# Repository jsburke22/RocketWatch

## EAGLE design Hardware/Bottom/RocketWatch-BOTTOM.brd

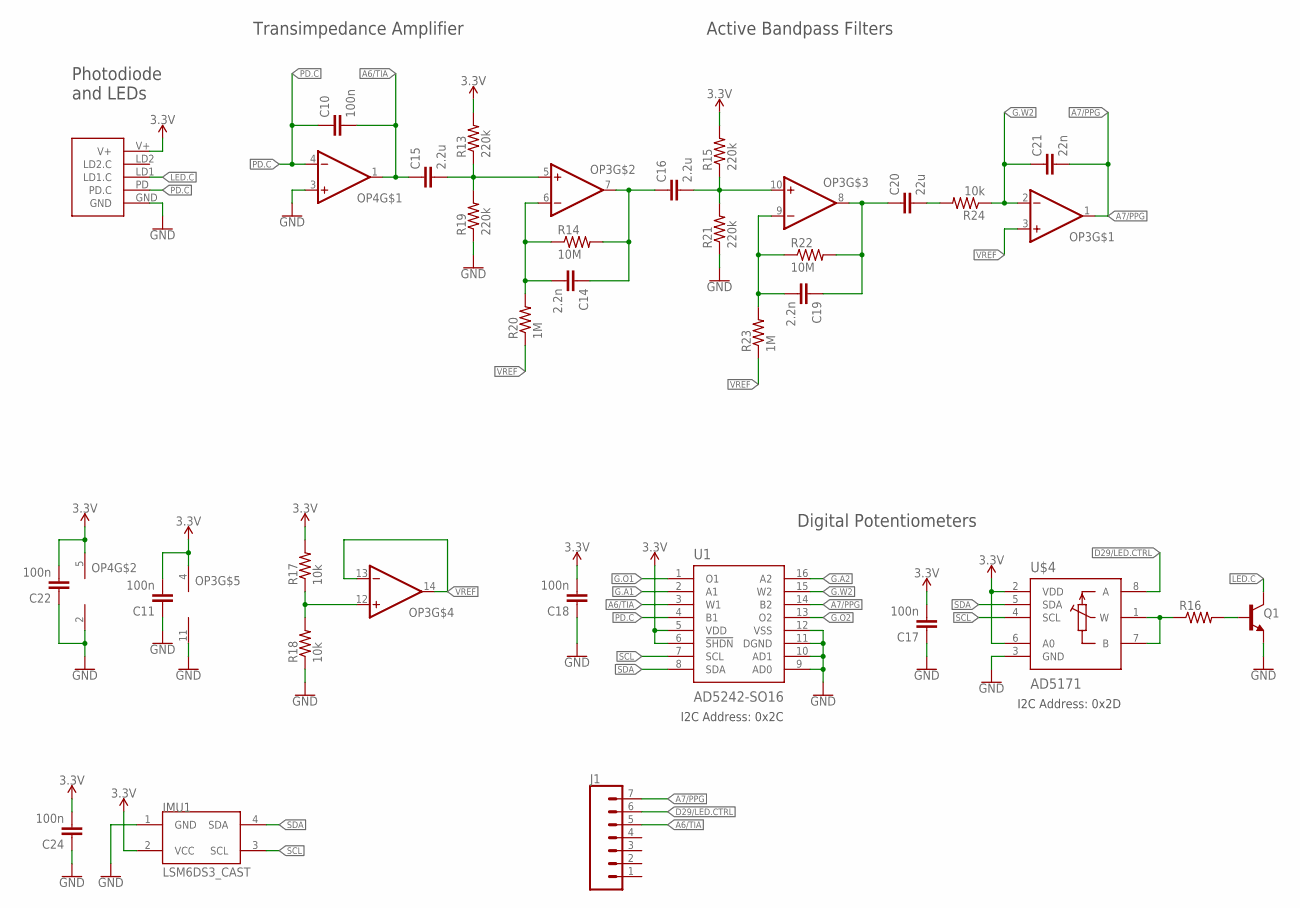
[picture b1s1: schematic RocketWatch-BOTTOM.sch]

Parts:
C10, C11, C17, C18, C22, C24: 100n; C0603
C14, C19: 2.2n; C0603
C15, C16: 2.2u; C0603
C20: 22u; C0603
C21: 22n; C0603
IMU1: LSM6DS3_CAST
J1: CONN_07; 1X07
OP3: OP-QUAD-SO14; SO14
OP4: OP-SINGLEOT; SOT23-5
Q1: NPN-GENERIC; SOT23-3
R13, R15, R19, R21: 220k; R0603
R14, R22: 10M; R0603
R16: RESISTOR0603; R0603
R17, R18: 10k; R0402
R20, R23: 1M; R0603
R24: 10k; R0603
U1: AD5242-SO16; SO16
U$3: PPG.MODULE.2
U$4: AD5171; SOT-23-8

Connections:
3.3V: C11.2, C17.2, C18.2, C22.2, C24.2, IMU1.2 (VCC), OP3.4 (V+), OP4.5 (V+), R13.2, R15.2, R17.2, U1.5 (VDD), U1.6 (!SHDN), U$3.V+, U$4.2 (VDD), U$4.6 (A0)
A6/TIA: C10.2, C15.1, J1.5, OP4.1 (OUT), U1.3 (W1)
A7/PPG: C21.2, J1.7, OP3.1 (OUT), U1.14 (B2)
D29/LED.CTRL: J1.6, U$4.8 (A)
G.A1: U1.2 (A1)
G.A2: U1.16 (A2)
G.O1: U1.1 (O1)
G.O2: U1.13 (O2)
G.W2: C21.1, OP3.2 (-IN), R24.1, U1.15 (W2)
GND: C11.1, C17.1, C18.1, C22.1, C24.1, IMU1.1 (GND), OP3.11 (V-), OP4.2 (V-), OP4.3 (+IN), Q1.2 (E), R18.1, R19.1, R21.1, U1.9 (AD0), U1.10 (AD1), U1.11 (DGND), U1.12 (VSS), U$3.GND, U$4.3 (GND)
LED.C: Q1.3 (C), U$3.LD1 (LD1.C)
unnamed: Q1.1 (B), R16.2
unnamed: R16.1, U$4.1 (W), U$4.7 (B)
unnamed: OP3.12 (+IN), R17.1, R18.2
unnamed: C15.2, OP3.5 (+IN), R13.1, R19.2
unnamed: C14.2, OP3.6 (-IN), R14.1, R20.2
unnamed: C14.1, C16.1, OP3.7 (OUT), R14.2
unnamed: C16.2, OP3.10 (+IN), R15.1, R21.2
unnamed: C19.2, OP3.9 (-IN), R22.1, R23.2
unnamed: C19.1, C20.1, OP3.8 (OUT), R22.2
unnamed: C20.2, R24.2
PD.C: C10.1, OP4.4 (-IN), U1.4 (B1), U$3.PD (PD.C)
SCL: IMU1.3 (SCL), U1.7 (SCL), U$4.4 (SCL)
SDA: IMU1.4 (SDA), U1.8 (SDA), U$4.5 (SDA)
VREF: OP3.3 (+IN), OP3.13 (-IN), OP3.14 (OUT), R20.1, R23.1

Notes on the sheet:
Photodiode and LEDs
Active Bandpass Filters
Digital Potentiometers
Transimpedance Amplifier
I2C Address: 0x2C
I2C Address: 0x2D

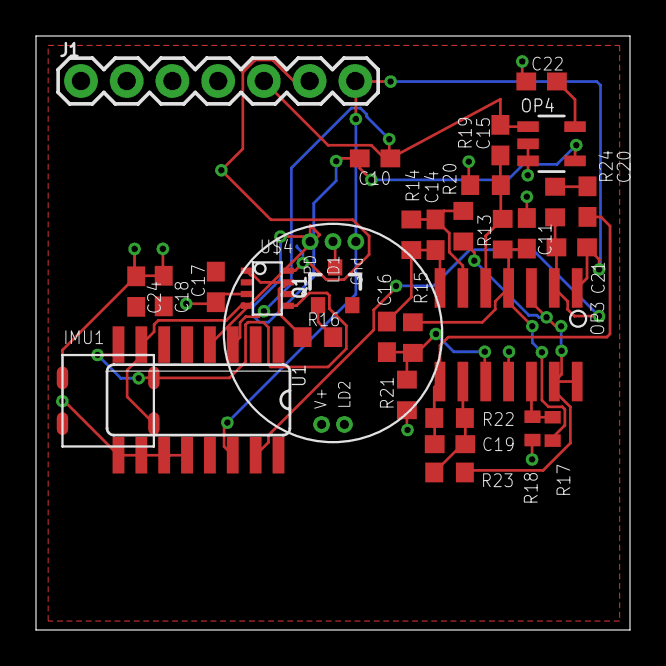
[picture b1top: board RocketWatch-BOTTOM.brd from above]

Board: 2 copper layers, 33.0 x 33.0 mm, 32 parts (0 on the bottom side), 21 nets.

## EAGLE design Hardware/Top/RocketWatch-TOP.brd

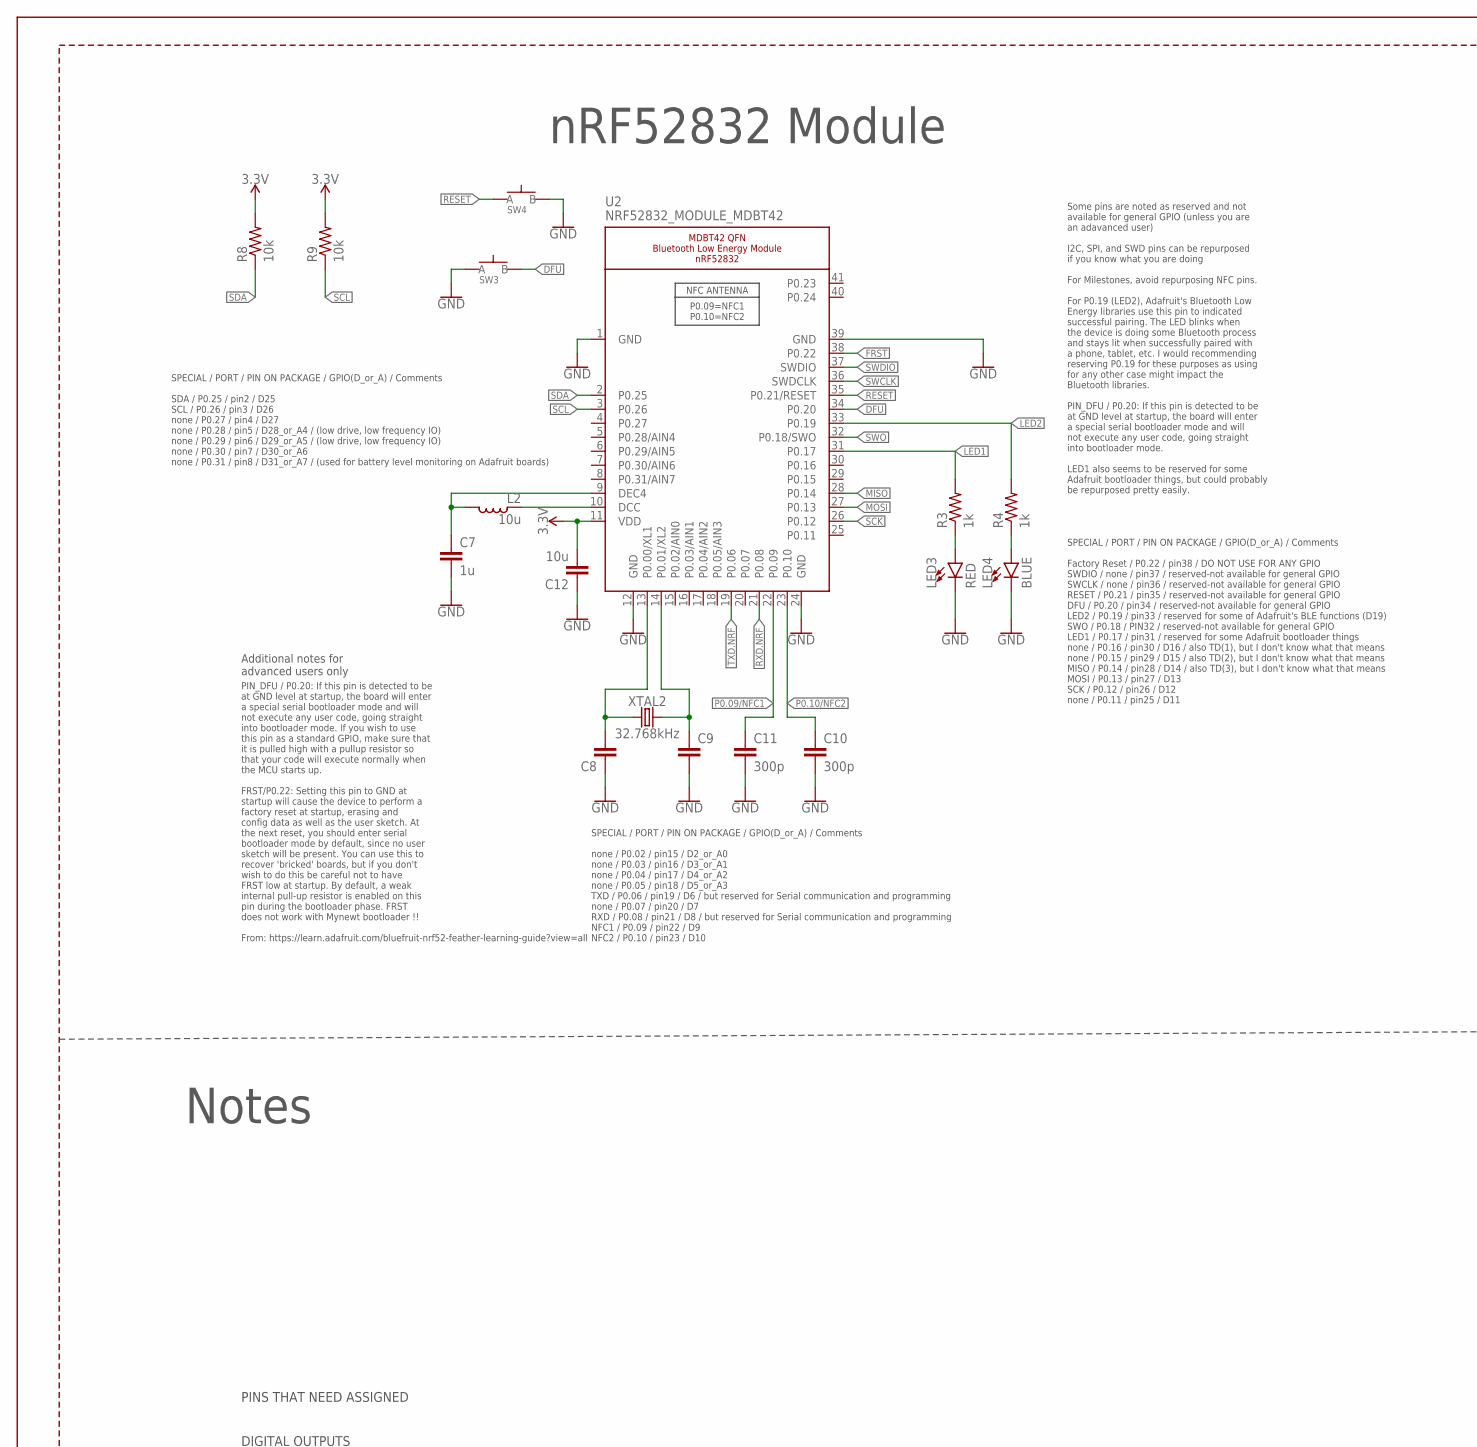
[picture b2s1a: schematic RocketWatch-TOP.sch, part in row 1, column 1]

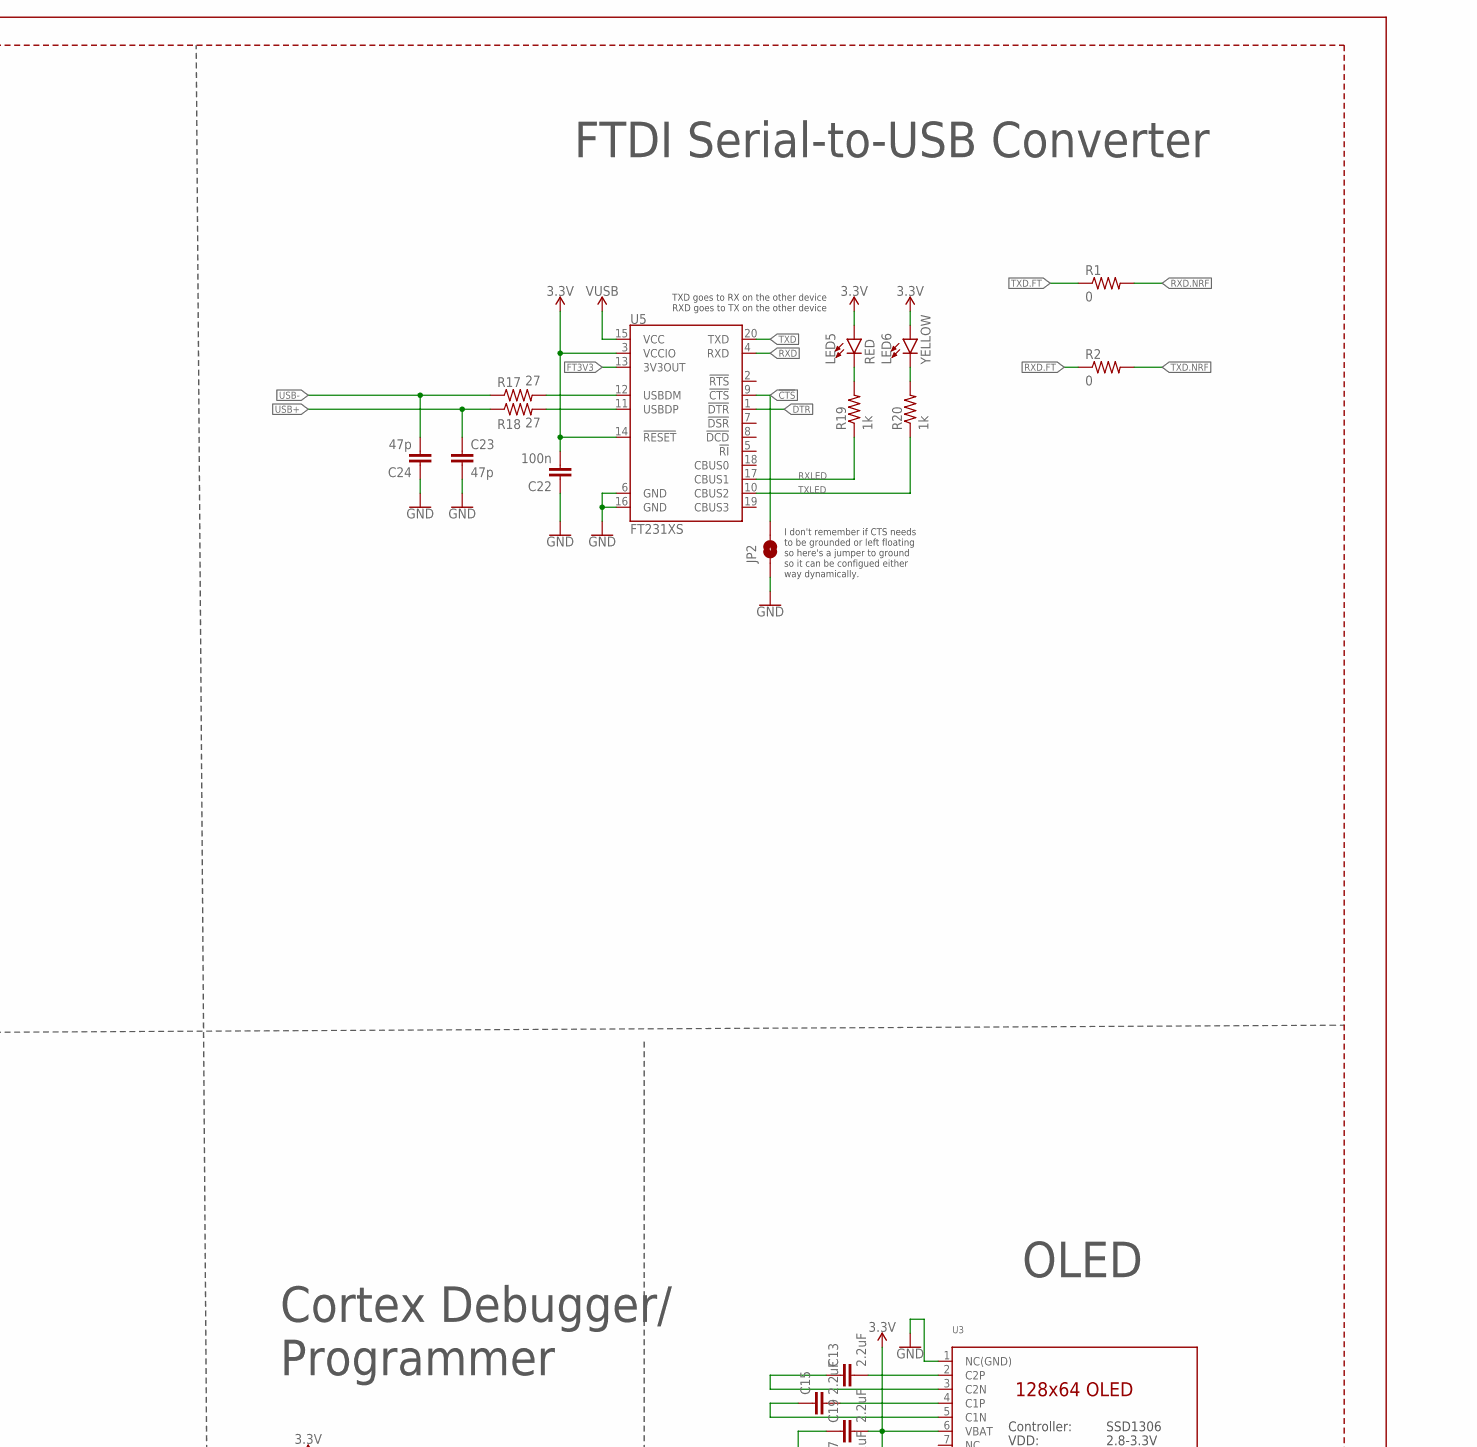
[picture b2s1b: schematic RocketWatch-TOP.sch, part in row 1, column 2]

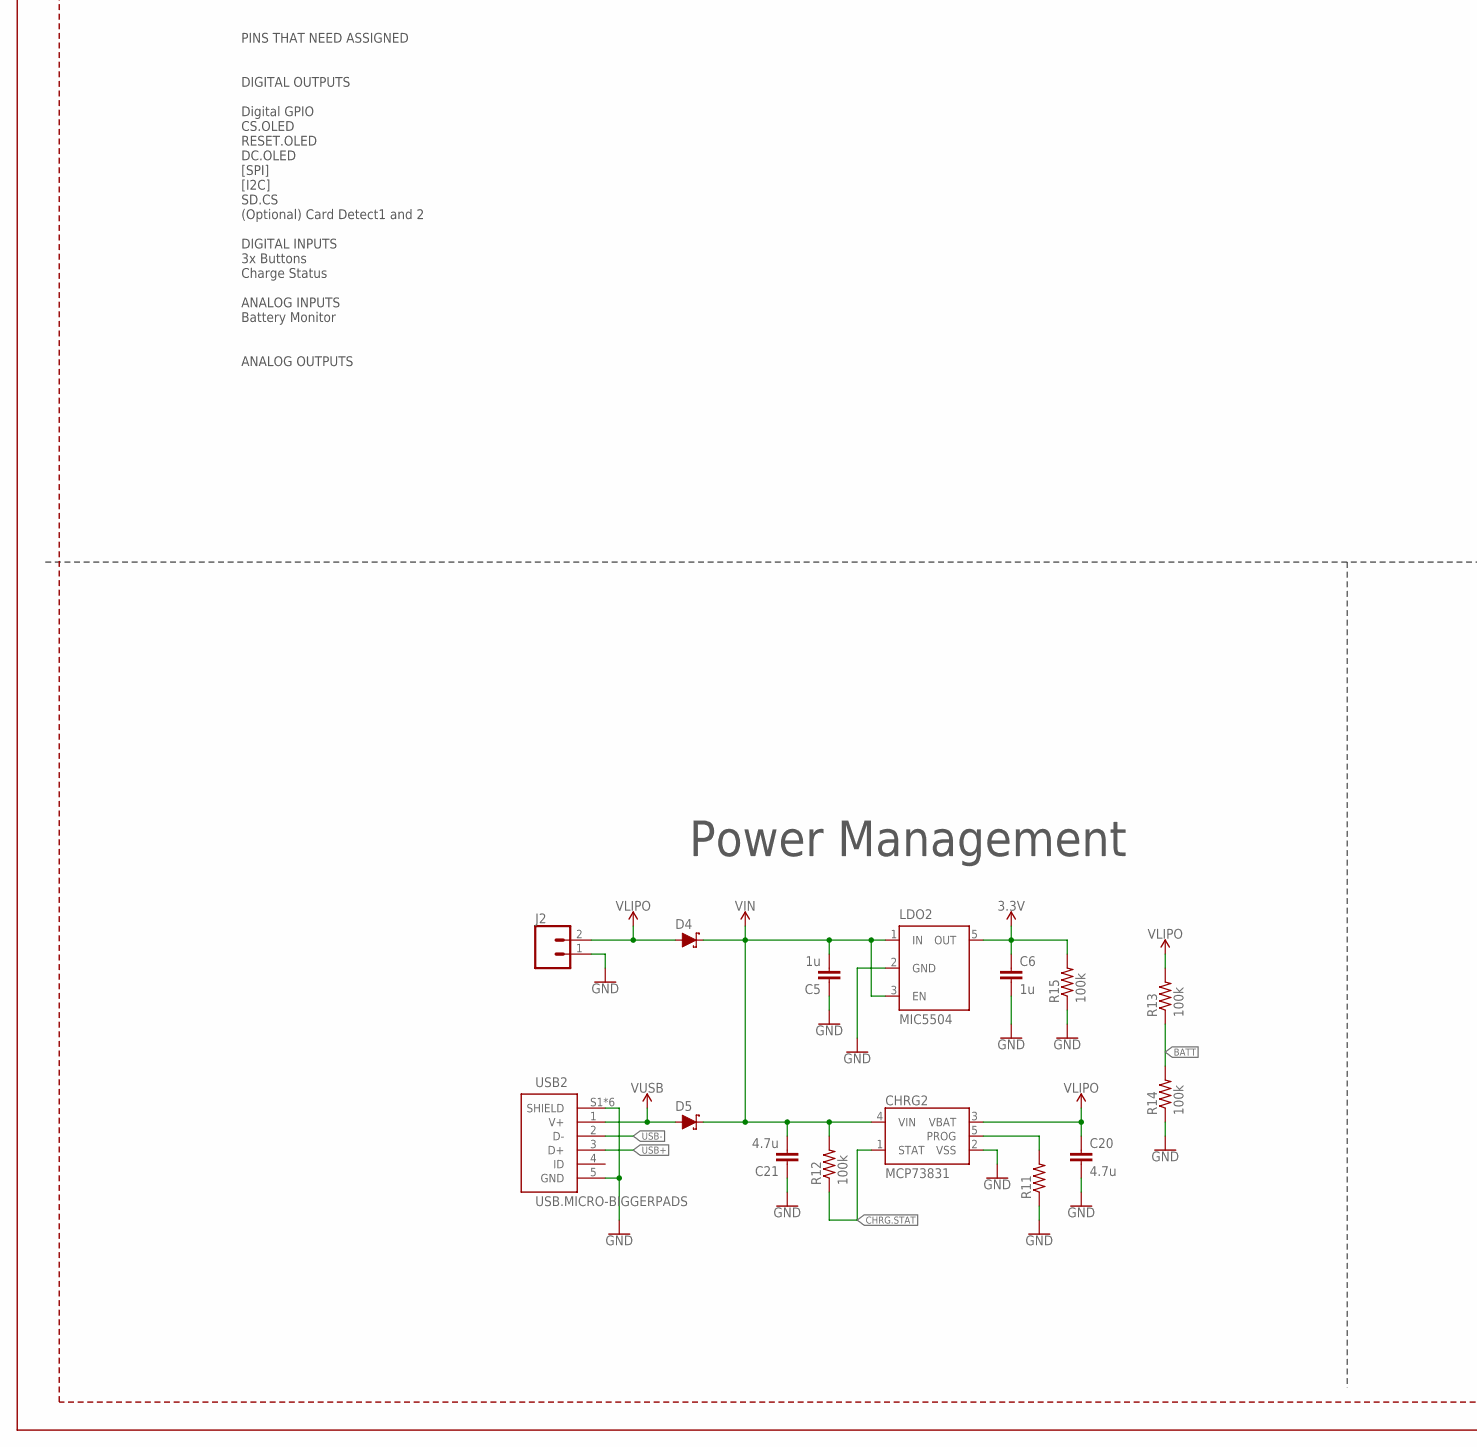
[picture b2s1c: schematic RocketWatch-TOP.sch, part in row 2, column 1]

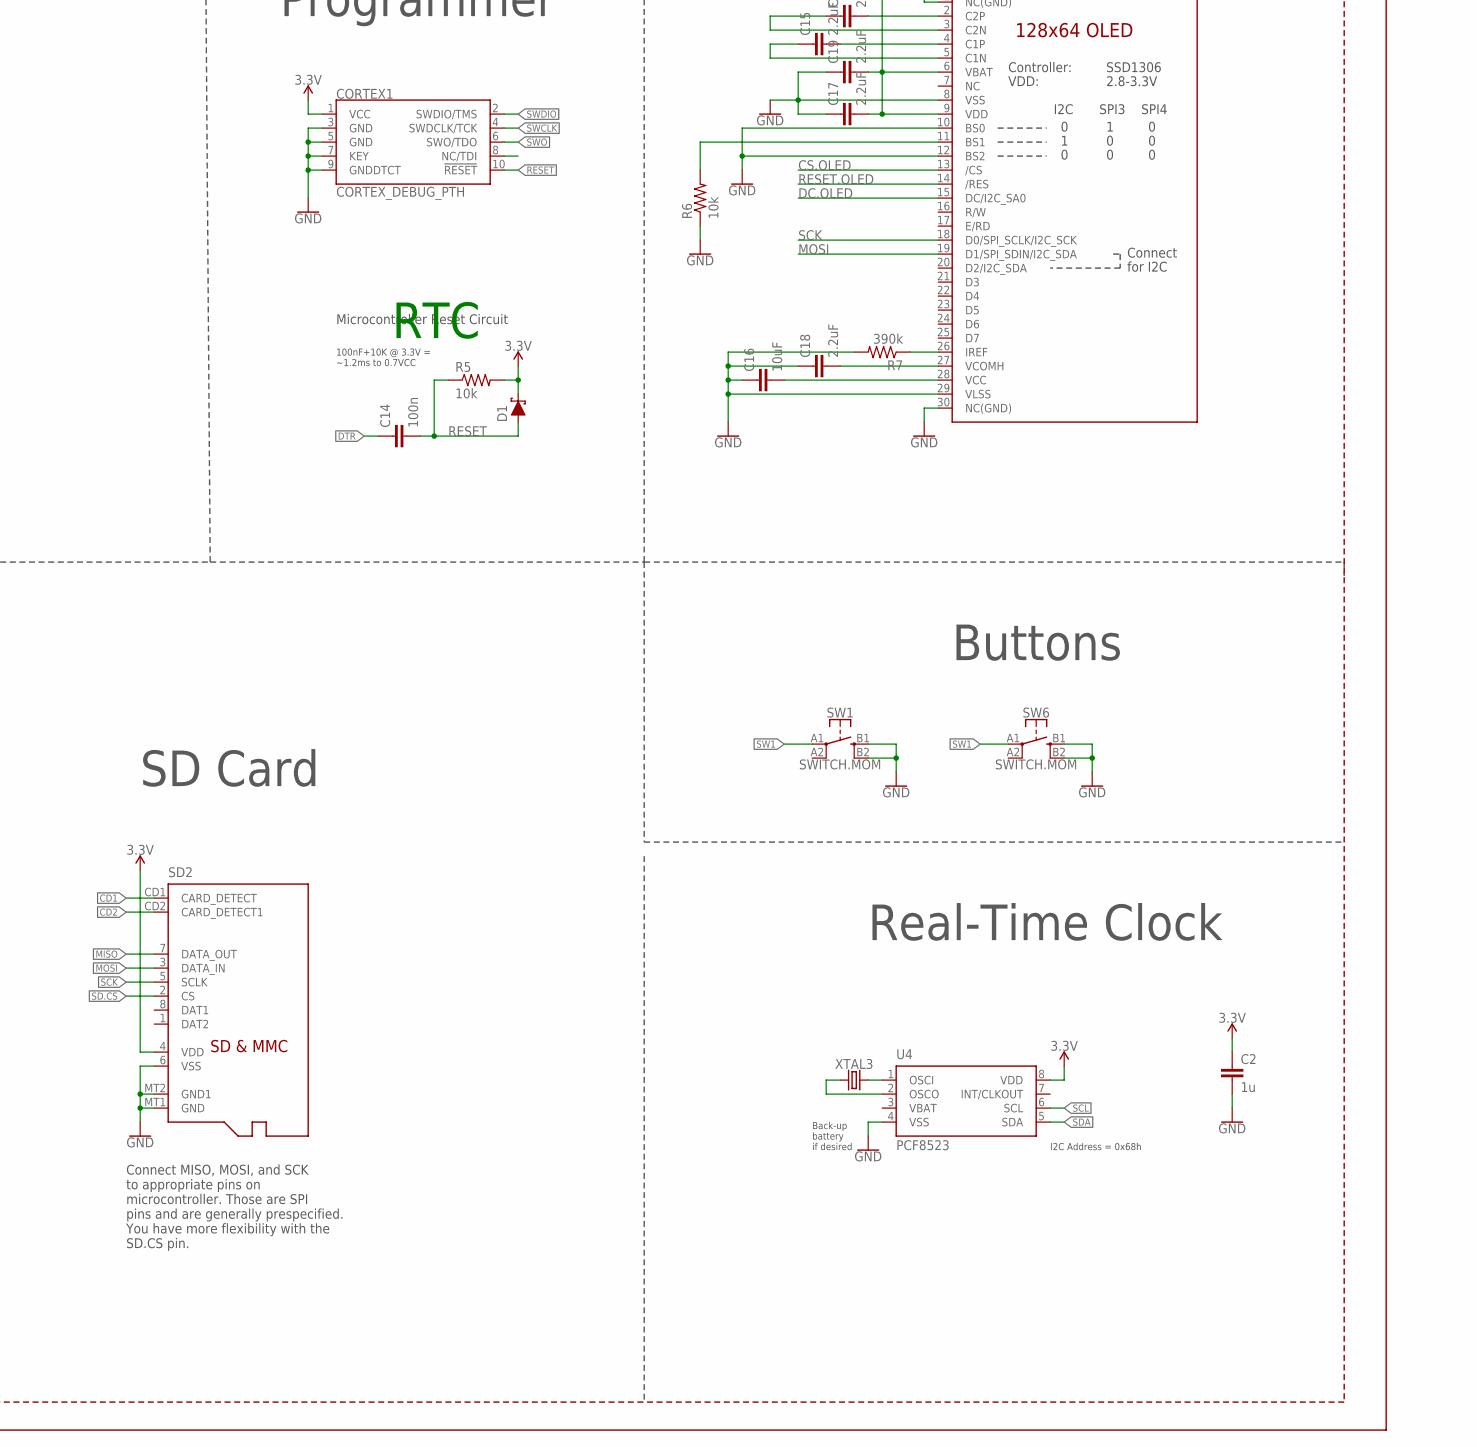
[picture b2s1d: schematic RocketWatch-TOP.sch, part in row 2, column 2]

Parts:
C2, C5, C6, C7: 1u; C0603
C8, C9: CAPACITOR0603; C0603
C10, C11: 300p; C0603
C12: 10u; C0805
C13, C15, C17, C18, C19: 2.2uF; C0402
C14, C22: 100n; C0603
C16: 10uF; C0603
C20, C21: 4.7u; C0603
C23, C24: 47p; C0603
CHRG2: MCP73831; SOT23-5
CORTEX1: CORTEX_DEBUG_PTH; 2X5-PTH-1.27MM
D1, D4, D5: SCHOTTKY-USC; USC
J2: CONN_02; 1X02
JP2: JUMPER-SMT_2_NO_SILK; SMT-JUMPER_2_NO_SILK
L2: 10u; L0603
LDO2: MIC5504; SOT23-5
LED3, LED5: RED; LED-0603
LED4: BLUE; LED-0603
LED6: YELLOW; LED-0603
R1, R2: 0; R0603
R3, R4, R19, R20: 1k; R0603
R5, R6, R8, R9: 10k; R0603
R7: 390k; R0603
R11: RESISTOR0603; R0603
R12, R13, R14, R15: 100k; R0603
R17, R18: 27; R0603
SD2: MICROSD
SW1, SW6: SWITCH.MOM; TACTILE_SWITCH_SMD_6.2MM_TALL
SW3, SW4: SPST-PTS830GG140-COPY.1-3; BUTTON-GULLWING
U2: NRF52832_MODULE_MDBT42; BLE_MODULE_RAYTAC_MDBT42
U3: DISP_OLED_UG-2864HSWEG01-NO-WRAPAROUND; UG-2864HSWEG01_0.96IN_NO-WRAPAROUND
U4: PCF8523; SO8; DIGIKEY 568-5306-1-ND
U5: FT231XS; SSOP20_L
USB2: USB.MICRO-BIGGERPADS; USB-MICRO-01.BIGGERPADS
XTAL2: 32.768kHz; 2-SMD.NOLEAD.2.0MMTO1.2MM
XTAL3: 32.7680kHz; 2-SMD.NOLEAD.2.0MMTO1.2MM

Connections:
3.3V: C2.1, C6.1, C12.2, C17.2, C19.2, C22.2, CORTEX1.1 (VCC), D1.- (C), LDO2.5 (OUT), LED5.A, LED6.A, R5.2, R8.2, R9.2, R15.2, SD2.4 (VDD), U2.11 (VDD), U3.6 (VBAT), U3.9 (VDD), U4.8 (VDD), U5.3 (VCCIO), U5.14 (!RESET)
!CTS: JP2.2, U5.9 (!CTS)
A4/BATT: R13.1, R14.2, U2.5 (P0.28/AIN4)
A6/TIA: U2.7 (P0.30/AIN6)
A7/PPG: U2.8 (P0.31/AIN7)
CD2: SD2.CD2 (CARD_DETECT1)
D3/RESET.OLED: U2.17 (P0.04/AIN2), U3.14 (/RES)
D4/DC.OLED: U2.16 (P0.03/AIN1), U3.15 (DC/I2C_SA0)
D5/CD1: SD2.CD1 (CARD_DETECT), U2.18 (P0.05/AIN3)
D7/SD.CS: SD2.2 (CS), U2.20 (P0.07)
D11/SW1: SW1.A1 (1), SW6.A1 (1), U2.25 (P0.11)
D15/SW2: U2.29 (P0.15); also elsewhere on the board
D16/CS.OLED: U2.30 (P0.16), U3.13 (/CS)
D27/CHRG.STATUS: CHRG2.1 (STAT), R12.1, U2.4 (P0.27)
D29/LED.CTRL: U2.6 (P0.29/AIN5)
DFU: SW3.3 (B), U2.34 (P0.20)
DTR: C14.1, U5.1 (!DTR)
FRST: U2.38 (P0.22)
FT3V3: U5.13 (3V3OUT)
GND: C2.2, C5.1, C6.2, C7.2, C8.1, C9.2, C10.2, C11.2, C12.1, C16.1, C17.1, C18.1, C19.1, C20.2, C21.1, C22.1, C23.2, C24.1, CHRG2.2 (VSS), CORTEX1.3 (GND), CORTEX1.5 (GND), CORTEX1.7 (KEY), CORTEX1.9 (GNDDTCT), J2.1, JP2.1, LDO2.2 (GND), LED3.C, LED4.C, R6.1, R7.2, R11.1, R14.1, R15.1, SD2.6 (VSS), SD2.MT1 (GND), SD2.MT2 (GND1), SW1.B1 (3), SW1.B2 (4), SW3.1 (A), SW4.3 (B), SW6.B1 (3), SW6.B2 (4), U2.1 (GND), U2.12 (GND), U2.24 (GND), U2.39 (GND), U3.1 (NC(GND)), U3.8 (VSS), U3.10 (BS0), U3.12 (BS2), U3.29 (VLSS), U3.30 (NC(GND)), U4.4 (VSS), U5.6 (GND), U5.16 (GND), USB2.5 (GND), USB2.S1 (SHIELD), USB2.S2 (SHIELD), USB2.S3 (SHIELD), USB2.S4 (SHIELD), USB2.S5 (SHIELD), USB2.S6 (SHIELD); also elsewhere on the board
LED1: R3.2, U2.31 (P0.17)
LED2: R4.2, U2.33 (P0.19)
MISO: SD2.7 (DATA_OUT), U2.28 (P0.14)
MOSI: SD2.3 (DATA_IN), U2.27 (P0.13), U3.19 (D1/SPI_SDIN/I2C_SDA)
unnamed: R6.2, U3.11 (BS1)
unnamed: R7.1, U3.26 (IREF)
unnamed: C13.2, U3.2 (C2P)
unnamed: C8.2, U2.13 (P0.00/XL1), XTAL2.P$1 (1)
unnamed: C13.1, U3.3 (C2N)
unnamed: C9.1, U2.14 (P0.01/XL2), XTAL2.P$2 (2)
unnamed: C15.2, U3.4 (C1P)
unnamed: C15.1, U3.5 (C1N)
unnamed: LED3.A, R3.1
unnamed: LED4.A, R4.1
unnamed: L2.1, U2.10 (DCC)
unnamed: C7.1, L2.2, U2.9 (DEC4)
unnamed: C16.2, U3.28 (VCC)
unnamed: C18.2, U3.27 (VCOMH)
unnamed: CHRG2.5 (PROG), R11.2
unnamed: U4.2 (OSCO), XTAL3.P$1 (1)
unnamed: U4.1 (OSCI), XTAL3.P$2 (2)
unnamed: R17.2, U5.12 (USBDM)
unnamed: R18.2, U5.11 (USBDP)
unnamed: LED5.C, R19.2
unnamed: LED6.C, R20.2
P0.09/NFC1: C11.1, U2.22 (P0.09)
P0.10/NFC2: C10.1, U2.23 (P0.10)
RESET: C14.2, CORTEX1.10 (!RESET), D1.+ (A), R5.1, SW4.1 (A), U2.35 (P0.21/RESET)
RXD: U5.4 (RXD)
RXD.FT: R2.1
RXD.NRF: R1.2, U2.21 (P0.08)
RXLED: R19.1, U5.17 (CBUS1)
SCK: SD2.5 (SCLK), U2.26 (P0.12), U3.18 (D0/SPI_SCLK/I2C_SCK)
SCL: R9.1, U2.3 (P0.26), U4.6 (SCL)
SDA: R8.1, U2.2 (P0.25), U4.5 (SDA)
SWCLK: CORTEX1.4 (SWDCLK/TCK), U2.36 (SWDCLK)
SWDIO: CORTEX1.2 (SWDIO/TMS), U2.37 (SWDIO)
SWO: CORTEX1.6 (SWO/TDO), U2.32 (P0.18/SWO)
TXD: U5.20 (TXD)
TXD.FT: R1.1
TXD.NRF: R2.2, U2.19 (P0.06)
TXLED: R20.1, U5.10 (CBUS2)
USB+: C23.1, R18.1, USB2.3 (D+)
USB-: C24.2, R17.1, USB2.2 (D-)
VBAT: U4.3 (VBAT)
VIN: C5.2, C21.2, CHRG2.4 (VIN), D4.- (C), D5.- (C), LDO2.1 (IN), LDO2.3 (EN), R12.2
VLIPO: C20.1, CHRG2.3 (VBAT), D4.+ (A), J2.2, R13.2
V_USB: D5.+ (A), U5.15 (VCC), USB2.1 (V+)

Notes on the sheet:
Microcontroller Reset Circuit
100nF+10K @ 3.3V = ~1.2ms to 0.7VCC
SPECIAL / PORT / PIN ON PACKAGE / GPIO(D_or_A) / Comments SDA / P0.25 / pin2 / D25 SCL / P0.26 / pin3 / D26 none / P0.27 / pin4 / D27 none / P0.28 / pin5 / D28_or_A4 / (low drive, low frequency IO) none / P0.29 / pin6 / D29_or_A5 / (low drive, low frequency IO) none / P0.30 / pin7 / D30_or_A6 none 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
SPECIAL / PORT / PIN ON PACKAGE / GPIO(D_or_A) / Comments none / P0.02 / pin15 / D2_or_A0 none / P0.03 / pin16 / D3_or_A1 none / P0.04 / pin17 / D4_or_A2 none / P0.05 / pin18 / D5_or_A3 TXD / P0.06 / pin19 / D6 / but reserved for Serial communication and programming none / P0.07 / pin20 / D7 RXD / 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
SPECIAL / PORT / PIN ON PACKAGE / GPIO(D_or_A) / Comments Factory Reset / P0.22 / pin38 / DO NOT USE FOR ANY GPIO SWDIO / none / pin37 / reserved-not available for general GPIO SWCLK / none / pin36 / reserved-not available for general GPIO RESET / P0.21 / pin35 / reserved-not available for general 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
Some pins are noted as reserved and not available for general GPIO (unless you are an adavanced user) I2C, SPI, and SWD pins can be repurposed if you know what you are doing For Milestones, avoid repurposing NFC pins. For P0.19 (LED2), Adafruit's Bluetooth Low Energy libraries use this pin to indic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
PIN_DFU / P0.20: If this pin is detected to be at GND level at startup, the board will enter a special serial bootloader mode and will not execute any user code, going straight into bootloader mode. If you wish to use this pin as a standard GPIO, make sure that it is pulled high with a pullup resis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
Additional notes for advanced users only
Connect MISO, MOSI, and SCK to appropriate pins on microcontroller. Those are SPI pins and are generally prespecified. You have more flexibility with the SD.CS pin.
I2C Address = 0x68h
Back-up battery if desired
nRF52832 Module
Buttons
Power Management
SD Card
Real-Time Clock
Cortex Debugger/ Programmer
RTC
OLED
PINS THAT NEED ASSIGNED DIGITAL OUTPUTS Digital GPIO CS.OLED RESET.OLED DC.OLED [SPI] [I2C] SD.CS (Optional) Card Detect1 and 2 DIGITAL INPUTS 3x Buttons Charge Status ANALOG INPUTS Battery Monitor ANALOG OUTPUTS
TXD goes to RX on the other device RXD goes to TX on the other device
I don't remember if CTS needs to be grounded or left floating so here's a jumper to ground so it can be configued either way dynamically.
FTDI Serial-to-USB Converter
Notes

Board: 2 copper layers, 64 parts (2 on the bottom side), 57 nets, no tracks yet.

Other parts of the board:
SW2: SWITCH.MOM; TACTILE_SWITCH_SMD_6.2MM_TALL

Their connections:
D15/SW2: SW2.A1; also elsewhere on the board
GND: SW2.B1, SW2.B2; also elsewhere on the board

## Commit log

2020-05-28 features list
2020-06-04 adding firmware and hardware files, as well as gitignore file
2020-06-04 updates to the board and schematic (added microcontroller, power management, OLED, Buttons, and a few other components)
2020-06-11 finished top schematic and board according to take 001 video
2020-06-11 finished initial layout of the bottom board and schematic
2020-06-11 changed schematic and board based on video take 002
2020-06-12 changes to top and bottom board based on take 002 video. Basic schematic and board is complete (no routing done yet)
2020-06-12 notes on different pin inputs/outputs and general notes about the EAGLE schematics
2020-06-12 adding V2 folders for a more complex board (currently the same as the basic board but will be edited in the future
2020-06-18 most of the bottom board routed. Few things left to route and clean up to show all labels.
2020-06-25 changes to firmware based on object oriented programming video
2020-06-25 Bottom board wired. DRC had some errors that still need fixed
